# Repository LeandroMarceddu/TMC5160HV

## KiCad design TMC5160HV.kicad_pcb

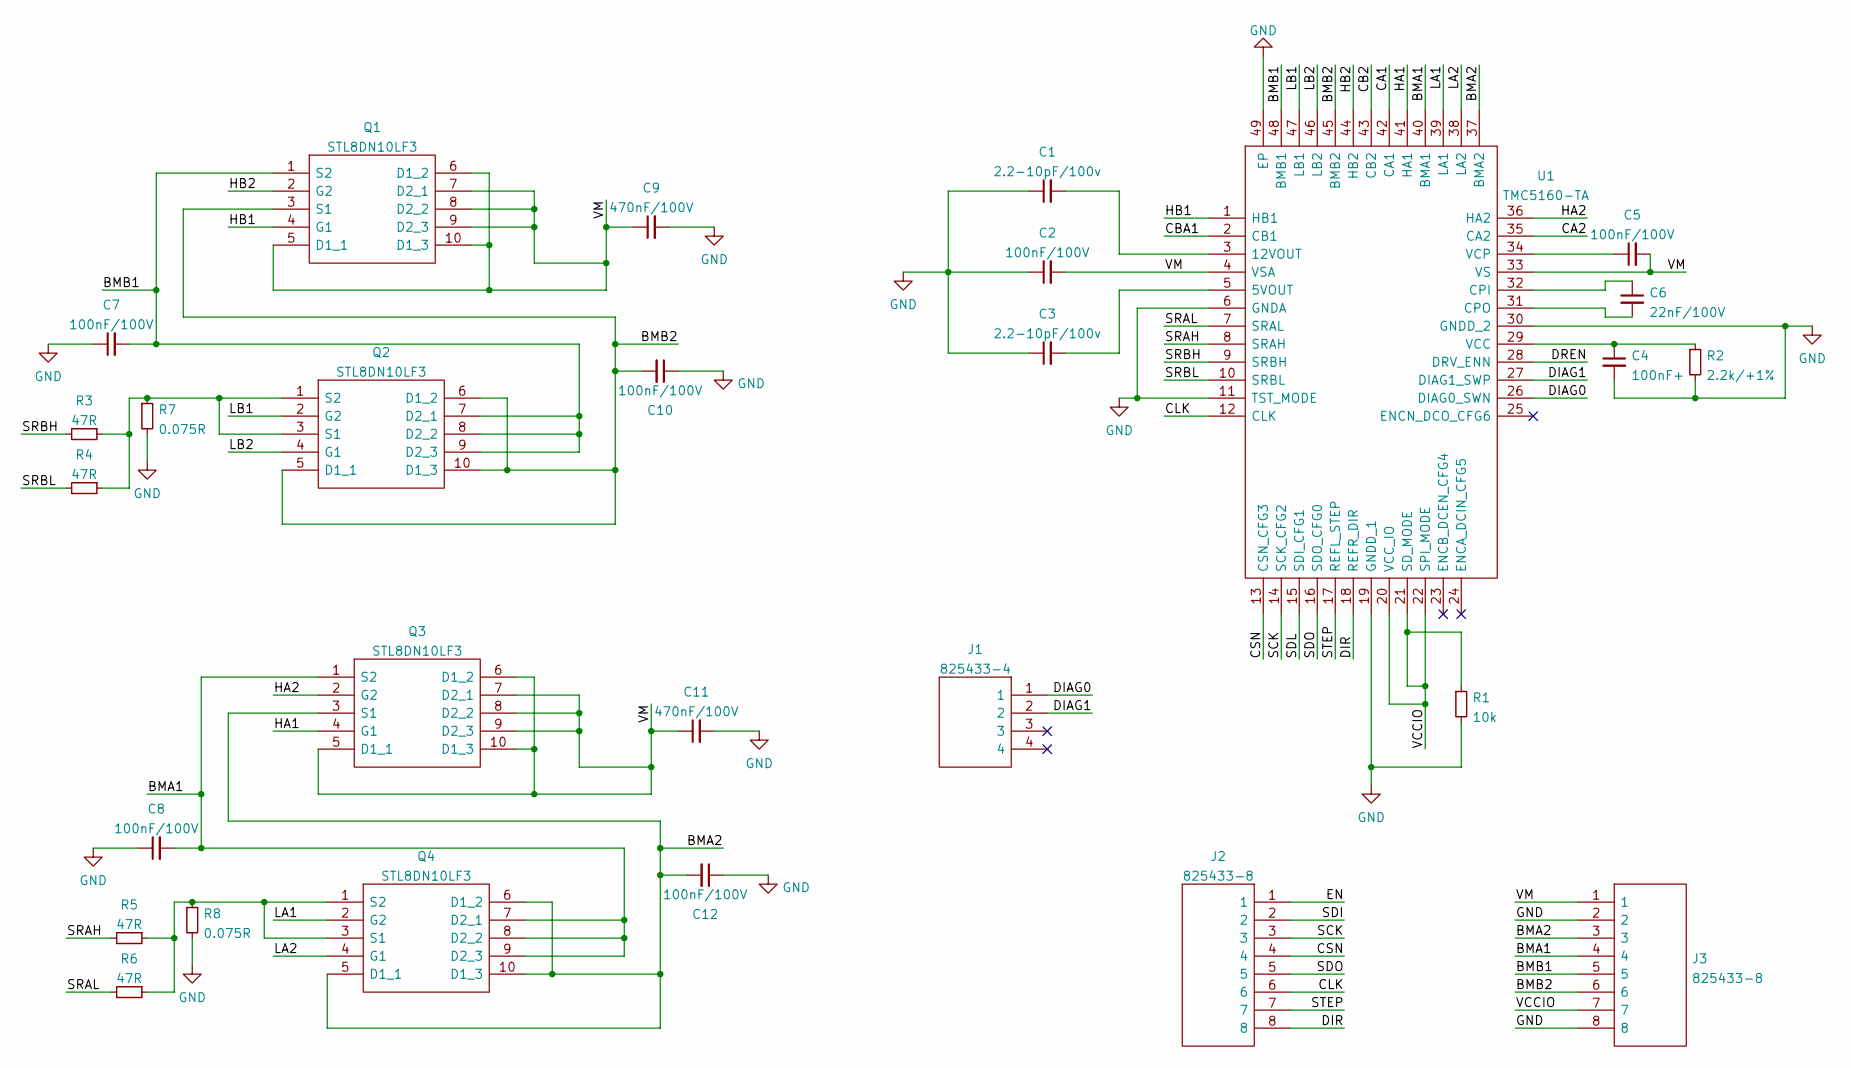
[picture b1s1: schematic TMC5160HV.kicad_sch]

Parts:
C1, C3: 2.2-10pF/100v; C_1206_3216Metric
C2, C5, C7, C8, C10, C12: 100nF/100V; C_1206_3216Metric
C4: 100nF+; C_1206_3216Metric
C6: 22nF/100V; C_1206_3216Metric
C9, C11: 470nF/100V; C_1206_3216Metric
J1: 825433-4; HDRV4W63P0X254_1X4_1016X250X950P; Manufacturer_Part_Number 825433-4; Mouser Part Number 571-825433-4
J2, J3: 825433-8; HDRV8W63P0X254_1X8_2032X254X970P; Manufacturer_Part_Number 825433-8; Mouser Part Number 571-825433-8
Q1, Q2, Q3, Q4: STL8DN10LF3; STL50DN6F7; Manufacturer_Part_Number STL8DN10LF3; Mouser Part Number 511-STL8DN10LF3
R1: 10k; R_0603_1608Metric
R2: 2.2k/+1%; R_0603_1608Metric
R3, R4, R5, R6: 47R; R_0603_1608Metric
R7, R8: 0.075R; R_0603_1608Metric
U1: TMC5160-TA; QFP50P900X900X120-49N; Manufacturer_Part_Number TMC5160-TA

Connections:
/BMA1: C8.2, J3.4, Q3.1 (S2), Q4.7 (D2_1), Q4.8 (D2_2), Q4.9 (D2_3), U1.40 (BMA1)
/BMA2: C12.2, J3.3, Q3.3 (S1), Q4.5 (D1_1), Q4.6 (D1_2), Q4.10 (D1_3), U1.37 (BMA2)
/BMB1: C7.2, J3.5, Q1.1 (S2), Q2.7 (D2_1), Q2.8 (D2_2), Q2.9 (D2_3), U1.48 (BMB1)
/BMB2: C10.2, J3.6, Q1.3 (S1), Q2.5 (D1_1), Q2.6 (D1_2), Q2.10 (D1_3), U1.45 (BMB2)
/CA1: U1.42 (CA1)
/CA2: U1.35 (CA2)
/CB2: U1.43 (CB2)
/CBA1: U1.2 (CB1)
/CLK: J2.6, U1.12 (CLK)
/CSN: J2.4, U1.13 (CSN_CFG3)
/DIAG0: J1.1, U1.26 (DIAG0_SWN)
/DIAG1: J1.2, U1.27 (DIAG1_SWP)
/DIR: J2.8, U1.18 (REFR_DIR)
/DREN: U1.28 (DRV_ENN)
/EN: J2.1
/HA1: Q3.4 (G1), U1.41 (HA1)
/HA2: Q3.2 (G2), U1.36 (HA2)
/HB1: Q1.4 (G1), U1.1 (HB1)
/HB2: Q1.2 (G2), U1.44 (HB2)
/LA1: Q4.2 (G2), U1.39 (LA1)
/LA2: Q4.4 (G1), U1.38 (LA2)
/LB1: Q2.2 (G2), U1.47 (LB1)
/LB2: Q2.4 (G1), U1.46 (LB2)
/SCK: J2.3, U1.14 (SCK_CFG2)
/SDI: J2.2
/SDL: U1.15 (SDI_CFG1)
/SDO: J2.5, U1.16 (SDO_CFG0)
/SRAH: R5.2, U1.8 (SRAH)
/SRAL: R6.2, U1.7 (SRAL)
/SRBH: R3.2, U1.9 (SRBH)
/SRBL: R4.2, U1.10 (SRBL)
/STEP: J2.7, U1.17 (REFL_STEP)
/VCCIO: J3.7, R1.1, U1.20 (VCC_IO), U1.21 (SD_MODE), U1.22 (SPI_MODE)
/VM: C2.2, C5.2, C9.1, C11.1, J3.1, Q1.5 (D1_1), Q1.6 (D1_2), Q1.7 (D2_1), Q1.8 (D2_2), Q1.9 (D2_3), Q1.10 (D1_3), Q3.5 (D1_1), Q3.6 (D1_2), Q3.7 (D2_1), Q3.8 (D2_2), Q3.9 (D2_3), Q3.10 (D1_3), U1.4 (VSA), U1.33 (VS)
GND: C1.1, C2.1, C3.1, C4.2, C7.1, C8.1, C9.2, C10.1, C11.2, C12.1, J3.2, J3.8, R1.2, R2.2, R7.2, R8.2, U1.6 (GNDA), U1.11 (TST_MODE), U1.19 (GNDD_1), U1.30 (GNDD_2), U1.49 (EP)
unnamed: C1.2, U1.3 (12VOUT)
unnamed: C3.2, U1.5 (5VOUT)
unnamed: C4.1, R2.1, U1.29 (VCC)
unnamed: C5.1, U1.34 (VCP)
unnamed: C6.1, U1.32 (CPI)
unnamed: C6.2, U1.31 (CPO)
unnamed: Q2.1 (S2), Q2.3 (S1), R3.1, R4.1, R7.1
unnamed: Q4.1 (S2), Q4.3 (S1), R5.1, R6.1, R8.1

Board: 2 copper layers, 28 parts (0 on the bottom side), 35 nets, no tracks yet.

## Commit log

2022-01-10 1206 for caps and 0603 for resistors
